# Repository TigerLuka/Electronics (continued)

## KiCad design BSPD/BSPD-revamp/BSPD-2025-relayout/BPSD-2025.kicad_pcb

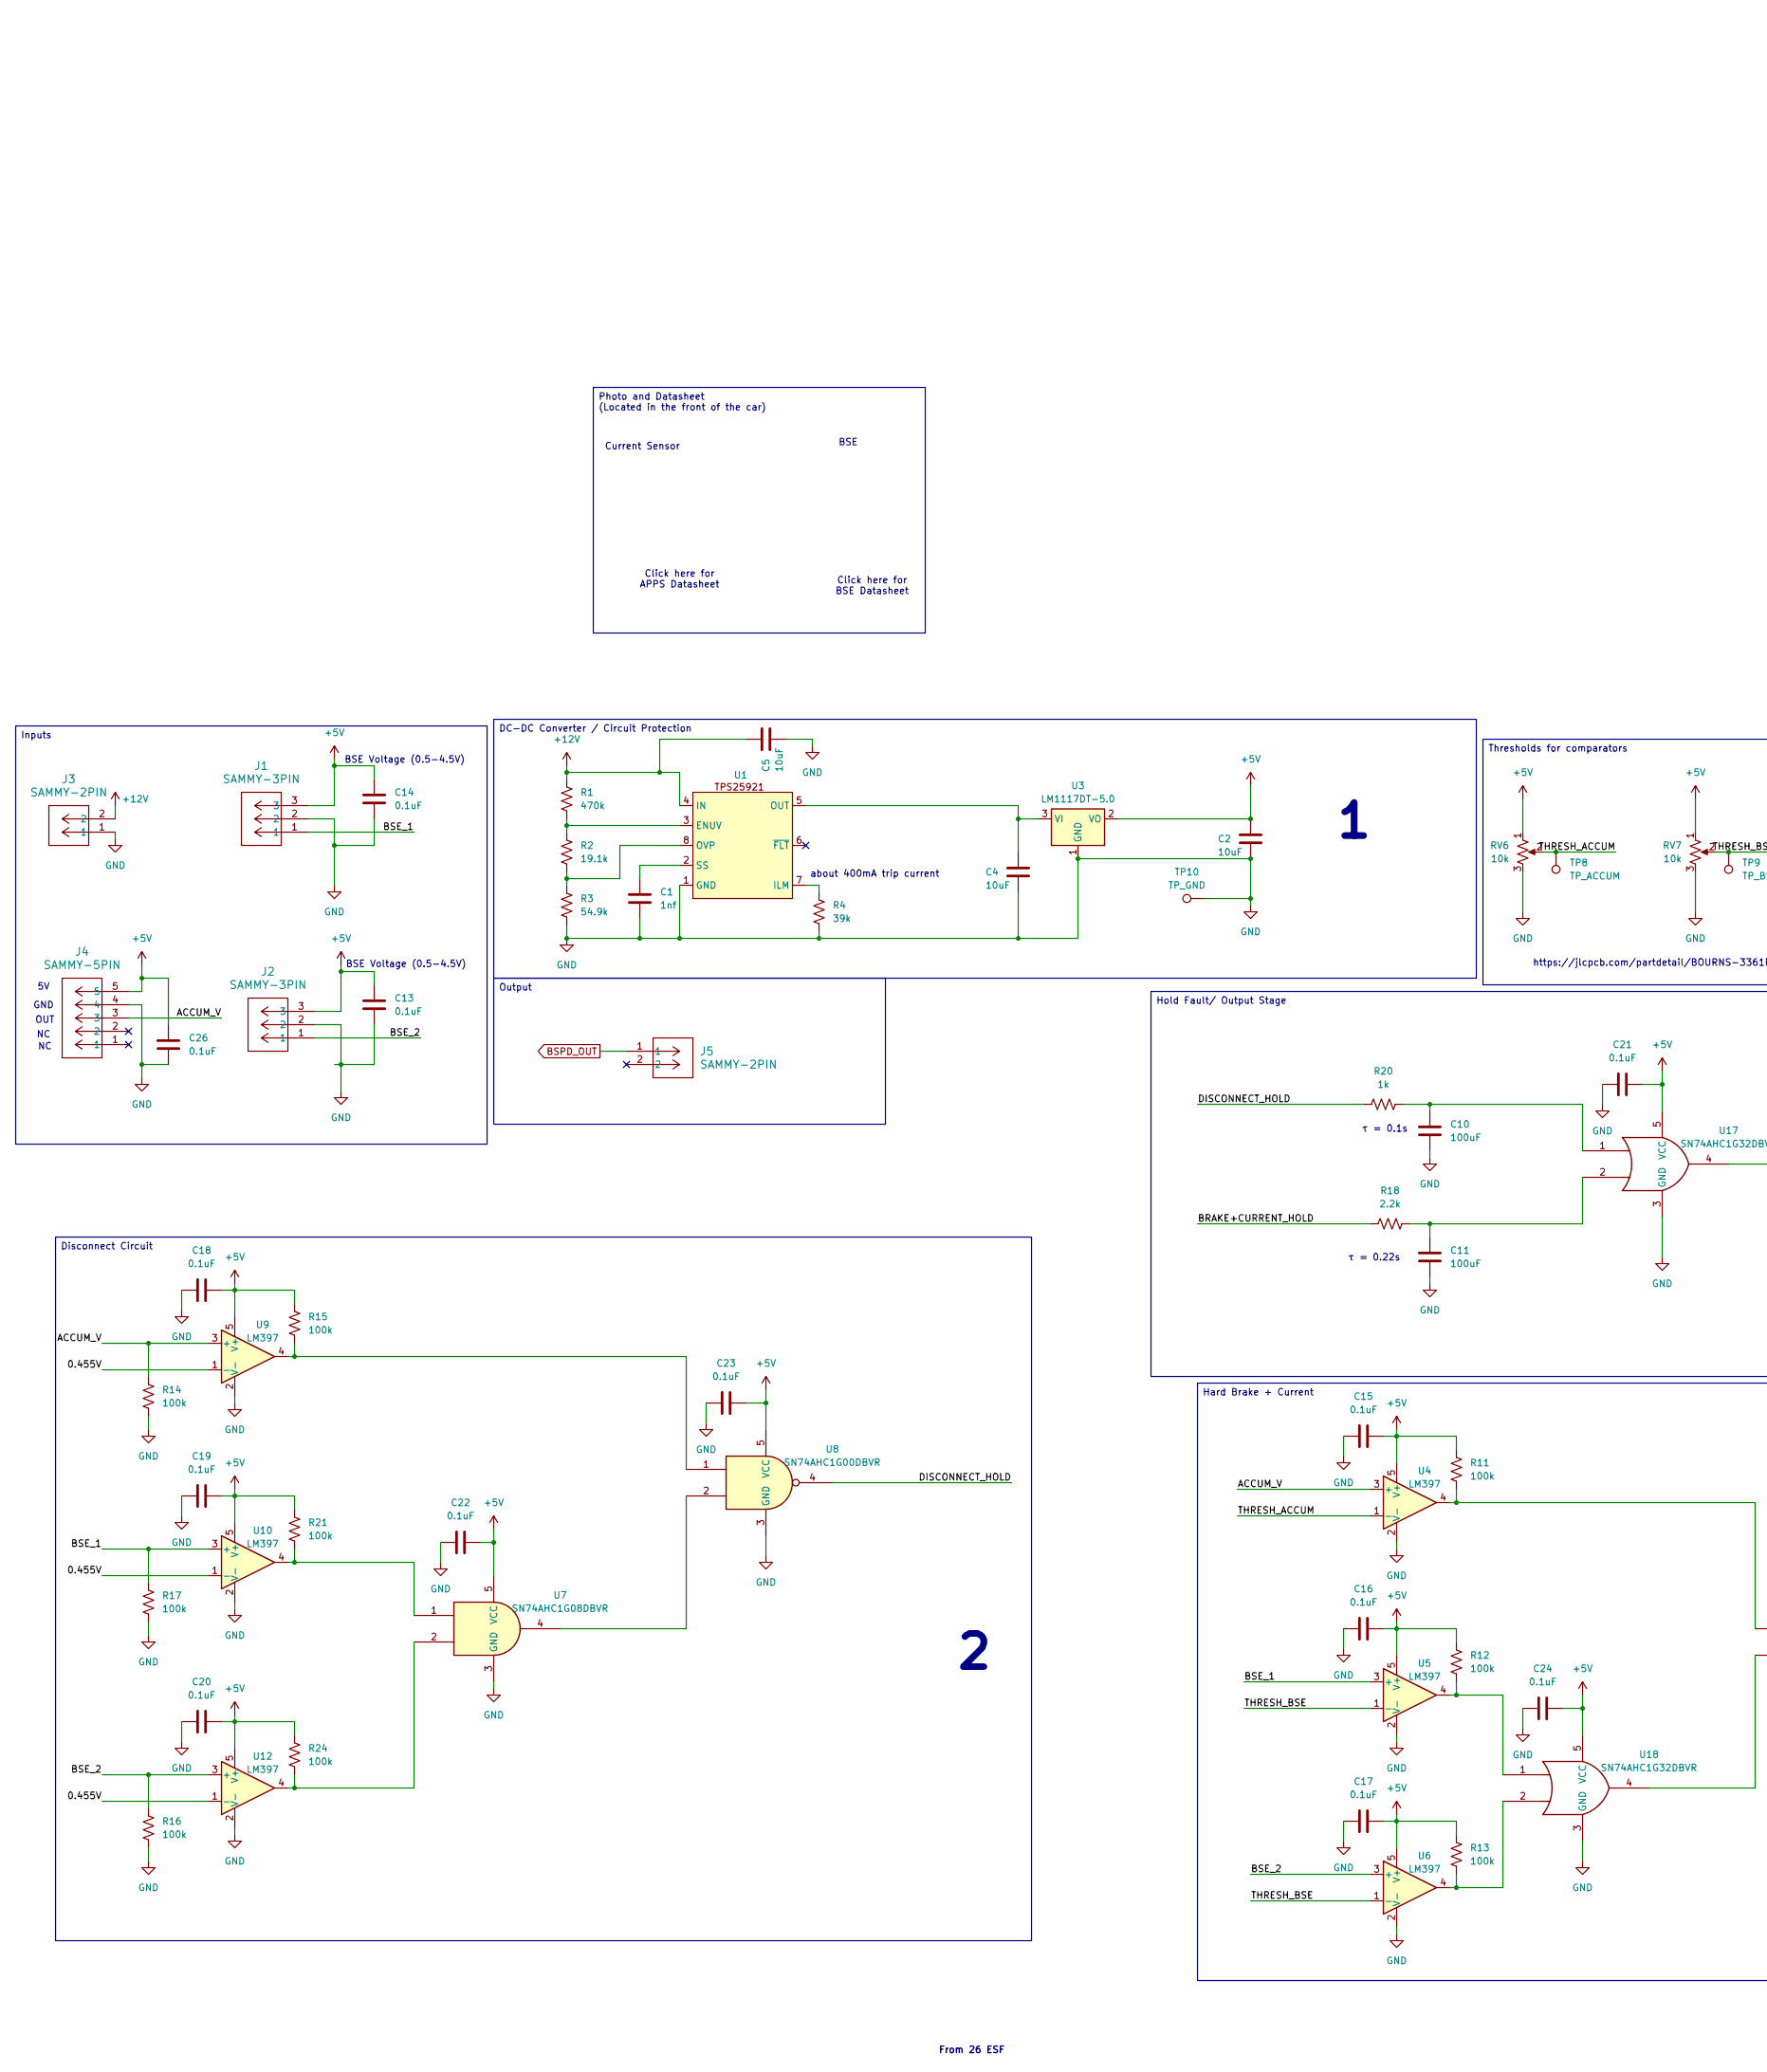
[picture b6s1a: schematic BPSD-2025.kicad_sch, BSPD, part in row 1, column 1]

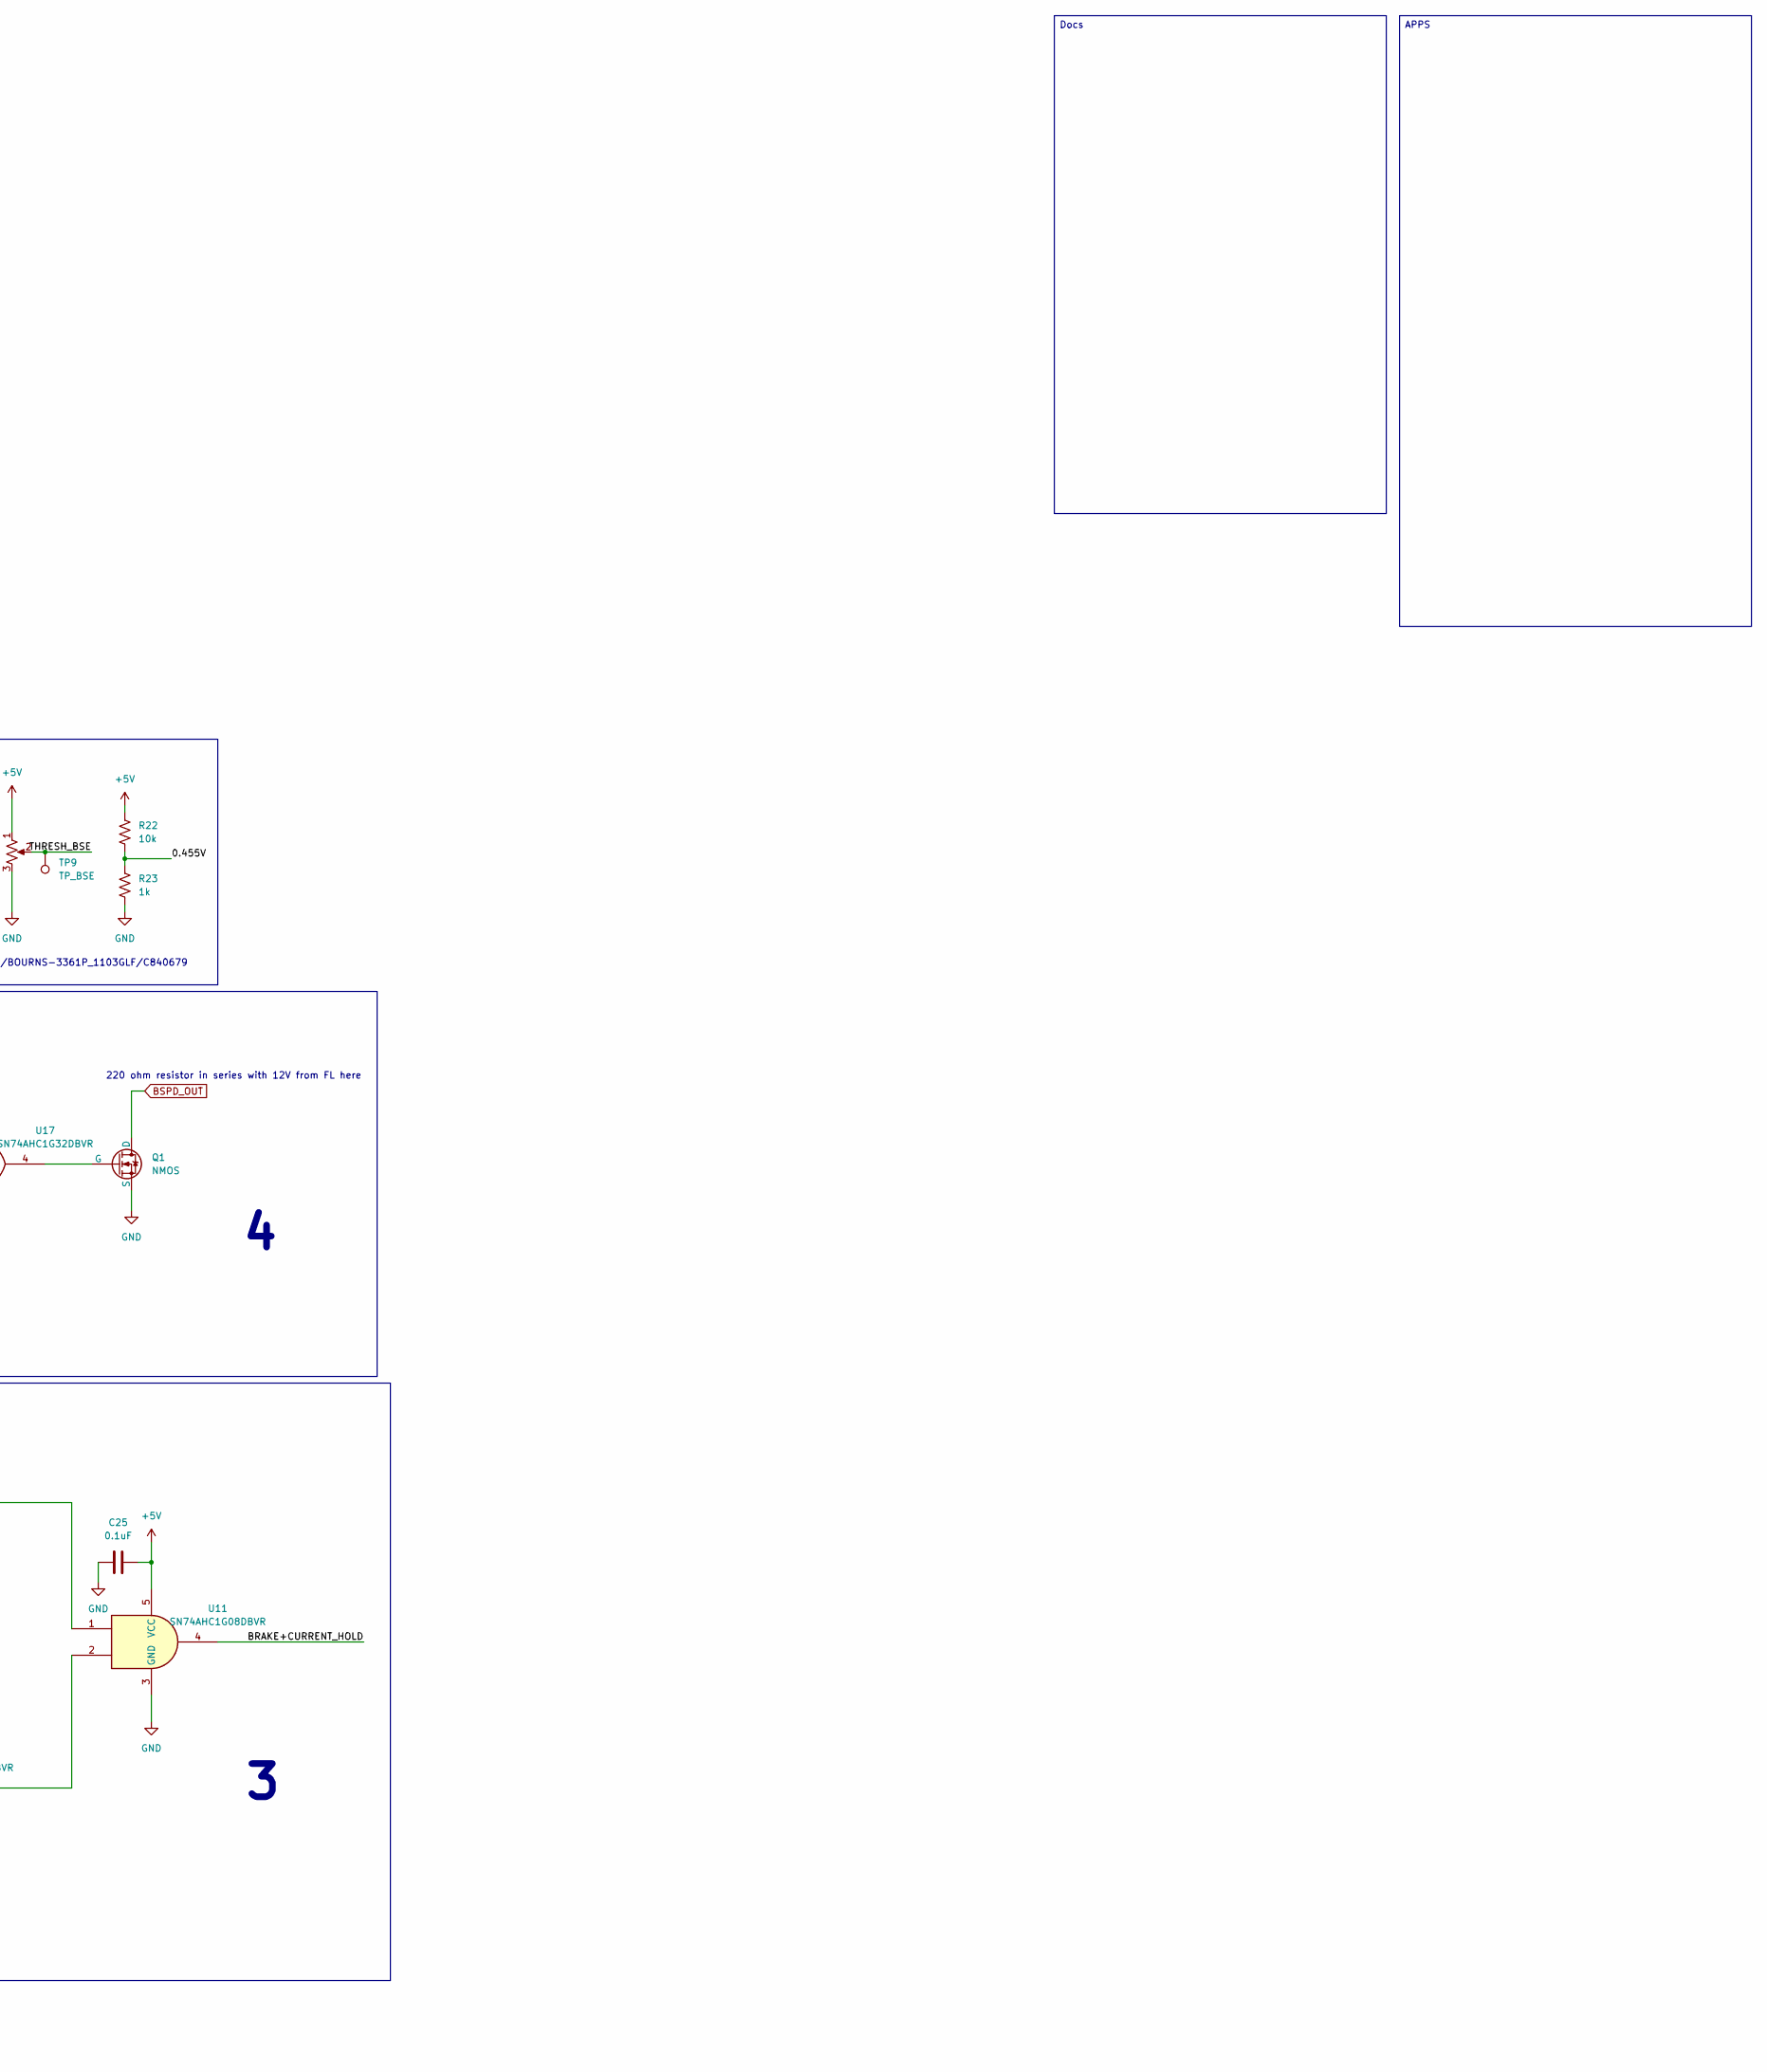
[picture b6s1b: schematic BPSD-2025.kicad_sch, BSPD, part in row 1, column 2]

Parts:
C1: 1nf; C_1206_3216Metric; JLC# C1845
C2, C4, C5: 10uF; C_1206_3216Metric; JLC# C1849
C10, C11: 100uF; C_1206_3216Metric; JLC# C782156
C13, C14, C15, C16, C17, C18, C19, C20, C21, C22, C23, C24, C25, C26: 0.1uF; C_1206_3216Metric; JLC# C1945
J1, J2: SAMMY-3PIN
J3, J5: SAMMY-2PIN
J4: SAMMY-5PIN
Q1: NMOS; SOT-23; JLC# C151421
R1: 470k; R_1210_3225Metric; JLC# C48392111
R2: 19.1k; R_1210_3225Metric; JLC# C784281
R3: 54.9k; R_1206_3216Metric; JLC# C323092
R4: 39k; R_1210_3225Metric; JLC# C728378
R11, R12, R13, R14, R15, R16, R17, R21, R24: 100k; R_1210_3225Metric; JLC# C230004
R18: 2.2k; R_1210_3225Metric; JLC# C230160
R20, R23: 1k; R_1210_3225Metric
R22: 10k; R_1210_3225Metric; JLC# C309586
RV6, RV7: 10k; Potentiometer_Bourns_3296W_Vertical; JLC# C118954
TP8: TP_ACCUM; TestPoint_Pad_D1.5mm
TP9: TP_BSE; TestPoint_Pad_D1.5mm
TP10: TP_GND; TestPoint_Pad_D1.5mm
U1: SOIC-8_3.9x4.9mm_P1.27mm; JLC# C189199
U3: LM1117DT-5.0; TO-252-3_TabPin2
U4, U5, U6, U9, U10, U12: LM397; SOT-23-5; JLC# C132076
U7, U11: SN74AHC1G08DBVR; SOT-23-5; JLC# C7467
U8: SN74AHC1G00DBVR; SOT-23-5; JLC# C350556
U17, U18: SN74AHC1G32DBVR; SOT-23-5; JLC# C7470

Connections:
+5V: C2.1, C13.1, C14.1, C15.2, C16.2, C17.2, C18.2, C19.2, C20.2, C21.2, C22.2, C23.2, C24.2, C25.2, C26.1, J1.3, J2.3, J4.5, R11.2, R12.2, R13.2, R15.2, R21.2, R22.2, R24.2, RV6.1, RV7.1, U3.2 (VO), U4.5 (V+), U5.5 (V+), U6.5 (V+), U7.5 (VCC), U8.5 (VCC), U9.5 (V+), U10.5 (V+), U11.5 (VCC), U12.5 (V+), U17.5 (VCC), U18.5 (VCC)
+12V: C5.1, J3.2, R1.1, U1.4 (IN)
/0.455V: R22.1, R23.2, U9.1 (-), U10.1 (-), U12.1 (-)
/ACCUM_V: J4.3, R14.2, U4.3 (+), U9.3 (+)
/BRAKE+CURRENT_HOLD: R18.1, U11.4
/BSE_1: J1.1, R17.2, U5.3 (+), U10.3 (+)
/BSE_2: J2.1, R16.2, U6.3 (+), U12.3 (+)
/DISCONNECT_HOLD: R20.1, U8.4
/THRESH_ACCUM: RV6.2, TP8.1, U4.1 (-)
/THRESH_BSE: RV7.2, TP9.1, U5.1 (-), U6.1 (-)
BSPD_OUT: J5.1, Q1.1 (D)
GND: C1.2, C2.2, C4.2, C5.2, C10.2, C11.2, C13.2, C14.2, C15.1, C16.1, C17.1, C18.1, C19.1, C20.1, C21.1, C22.1, C23.1, C24.1, C25.1, C26.2, J1.2, J2.2, J3.1, J4.4, Q1.3 (S), R3.2, R4.2, R14.1, R16.1, R17.1, R23.1, RV6.3, RV7.3, TP10.1, U1.1 (GND), U3.1 (GND), U4.2 (V-), U5.2 (V-), U6.2 (V-), U7.3 (GND), U8.3 (GND), U9.2 (V-), U10.2 (V-), U11.3 (GND), U12.2 (V-), U17.3 (GND), U18.3 (GND)
unnamed: C10.1, R20.2, U17.1
unnamed: C11.1, R18.2, U17.2
unnamed: Q1.2 (G), U17.4
unnamed: R11.1, U4.4, U11.1
unnamed: R12.1, U5.4, U18.1
unnamed: R13.1, U6.4, U18.2
unnamed: R15.1, U8.1, U9.4
unnamed: R21.1, U7.1, U10.4
unnamed: R24.1, U7.2, U12.4
unnamed: R1.2, R2.1, U1.3 (ENUV)
unnamed: R4.1, U1.7 (ILM)
unnamed: C4.1, U1.5 (OUT), U3.3 (VI)
unnamed: R2.2, R3.1, U1.8 (OVP)
unnamed: C1.1, U1.2 (SS)
unnamed: U7.4, U8.2
unnamed: U11.2, U18.4

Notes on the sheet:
BSE Voltage (0.5-4.5V)
BSE
GND
220 ohm resistor in series with 12V from FL here
about 400mA trip current
τ = 0.1s
Click here for APPS Datasheet
OUT
https://jlcpcb.com/partdetail/BOURNS-3361P_1103GLF/C840679
τ = 0.22s
From 26 ESF
Current Sensor
Click here for BSE Datasheet
Inputs
Hard Brake + Current
Docs
APPS
Photo and Datasheet (Located in the front of the car)
DC-DC Converter / Circuit Protection
Disconnect Circuit
Hold Fault/ Output Stage
Thresholds for comparators
Output

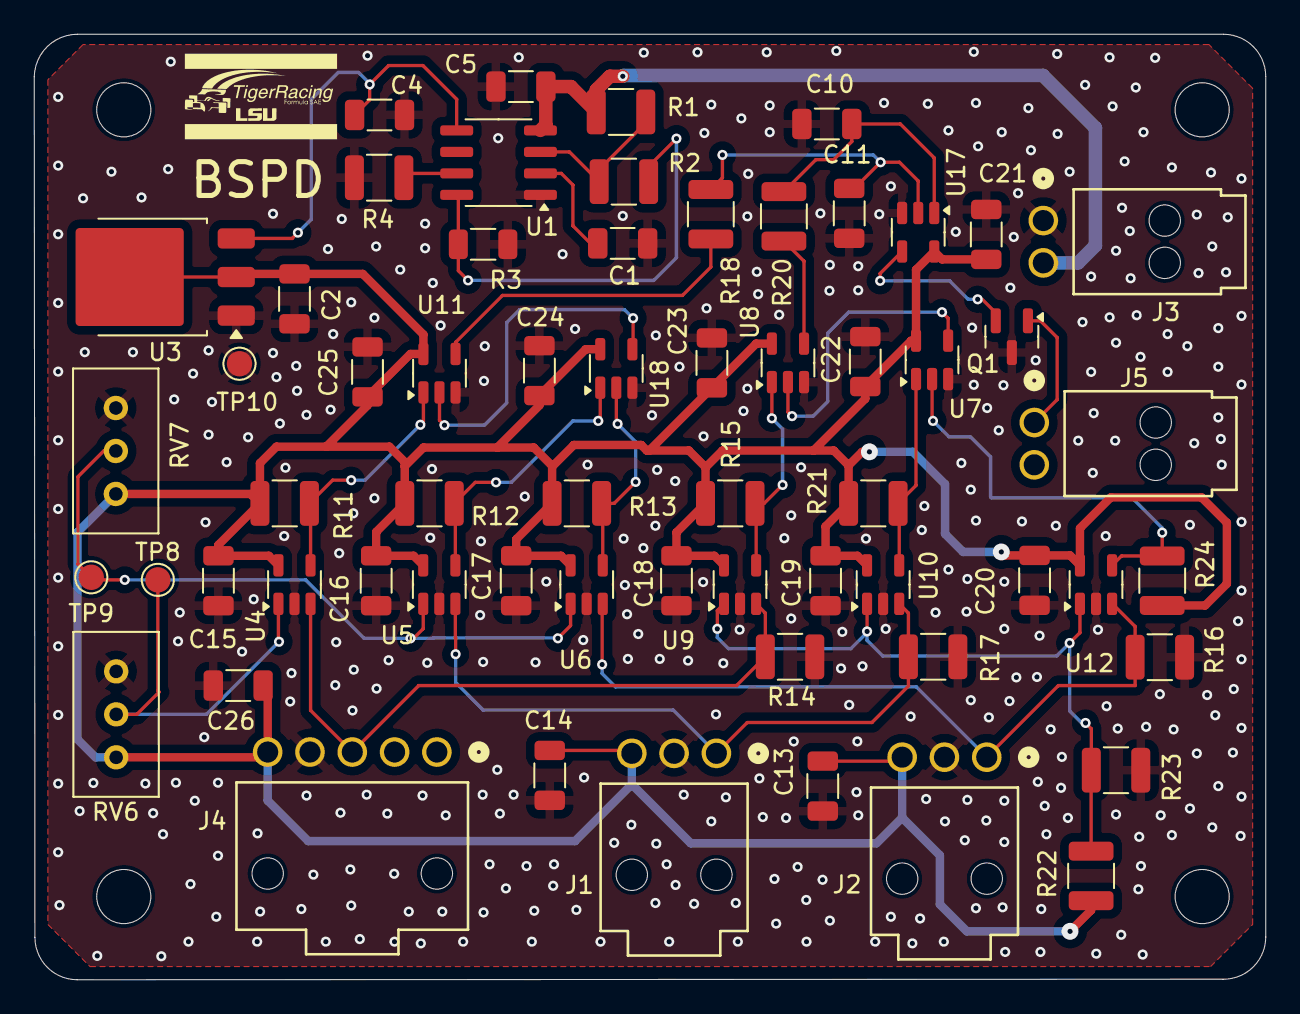
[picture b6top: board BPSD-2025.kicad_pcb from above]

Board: 2 copper layers, 72.8 x 55.9 mm, 61 parts (0 on the bottom side), 28 nets.

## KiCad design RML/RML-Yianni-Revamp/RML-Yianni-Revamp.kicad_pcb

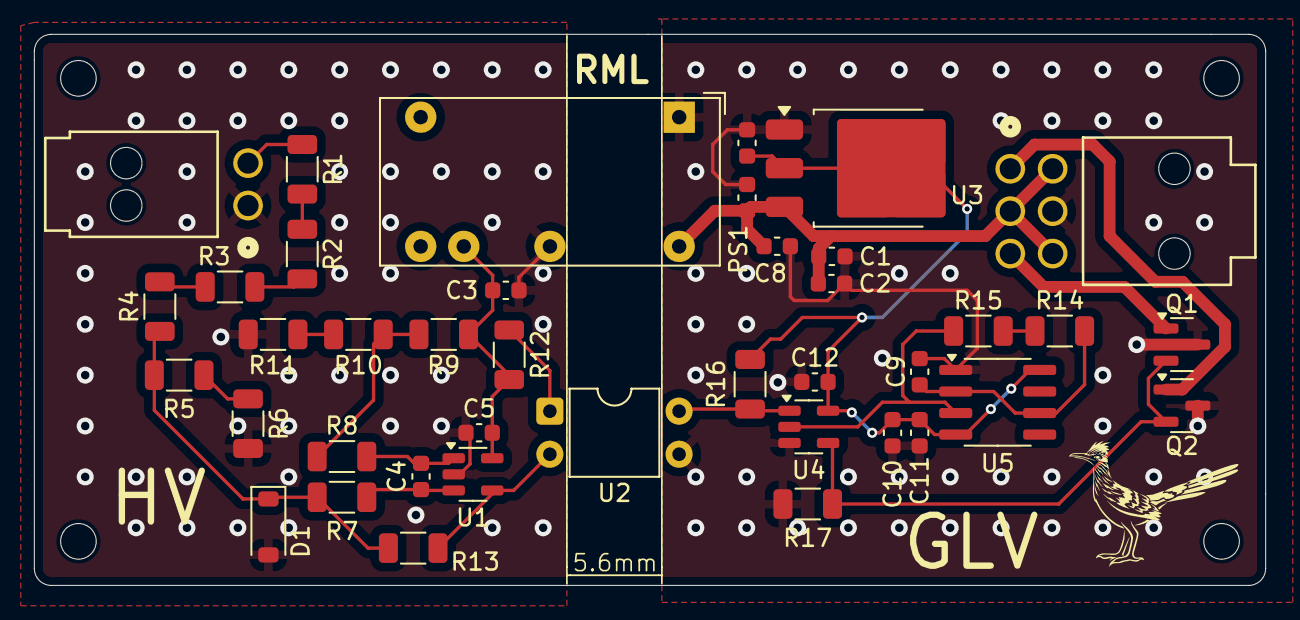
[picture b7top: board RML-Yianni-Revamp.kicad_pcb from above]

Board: 2 copper layers, 72.6 x 32.5 mm, 40 parts (0 on the bottom side), 24 nets.

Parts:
C1, C3, C4, C6, C7: 10u; C_0603_1608Metric
C2, C8, C9, C10: 1u; C_0603_1608Metric
C5, C11, C12: 100n; C_0603_1608Metric
D1: 12V; D_SOD-123
J1: Tractive; SAMMY-2PIN
J3: SAMMY-6PIN
PS1: IA1212D; Converter_DCDC_XP_POWER-IAxxxxD_THT
Q1, Q2: NMOS; SOT-23
R1, R2, R3, R4: 249k; R_1206_3216Metric
R5: 49k9; R_1206_3216Metric
R6: 2k2; R_1206_3216Metric
R7, R8: 100; R_1206_3216Metric
R9: 75k; R_1206_3216Metric
R10: 24k; R_1206_3216Metric
R11: 900; R_1206_3216Metric
R12: 1k; R_1206_3216Metric
R13: 1M; R_1206_3216Metric
R14: 47k; R_1206_3216Metric
R15, R17: 100k; R_1206_3216Metric
R16: 10k; R_1206_3216Metric
U1: LM397; SOT-23-5
U2: SFH617A-1; DIP-4_W7.62mm
U3: LM1117DT-5.0; TO-252-3_TabPin2
U4: 74AHC1G02; SOT-23-5
U5: LM555xM; SOIC-8_3.9x4.9mm_P1.27mm

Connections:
+5V: C7.1, C10.1, C11.1, C12.2, R16.1, U3.2 (VO), U4.5 (VCC), U5.4 (R), U5.8 (VCC)
+12V: C1.1, C2.1, C6.1, C8.1, J3.2, J3.4, J3.6, PS1.3 (+Vin), U3.3 (VI)
/ISO_+12V: C3.1, C5.2, PS1.5 (+Vout), R9.1, R12.2, U1.5 (V+)
/RML1-: J3.3, Q1.1 (D)
/RML2-: J3.1, Q2.1 (D)
/THRESH: C9.1, R14.1, U5.2 (TR), U5.6 (THR)
/TS+: J1.2, R1.1
/Vref: R8.1, R9.2, R10.1
CLOCK: R15.2, U4.2, U5.3 (Q)
GND: C1.2, C2.2, C6.2, C7.2, C8.2, C9.2, C10.2, C11.2, C12.1, J3.5, PS1.1 (-Vin), Q1.3 (S), Q2.3 (S), R17.1, U2.3, U3.1 (GND), U4.3 (GND), U5.1 (GND)
GNDPWR: C3.2, C5.1, D1.2 (A), J1.1, PS1.4 (-Vout), R6.2, R11.2, U1.2 (V-)
unnamed: D1.1 (K), R4.2, R5.1, R7.1, R13.1
unnamed: Q1.2 (G), Q2.2 (G), R17.2, U4.4
unnamed: R1.2, R2.1
unnamed: R2.2, R3.1
unnamed: R3.2, R4.1
unnamed: R5.2, R6.1
unnamed: R10.2, R11.1
unnamed: R12.1, U2.1
unnamed: R13.2, U1.4, U2.2
unnamed: R14.2, R15.1
unnamed: R16.2, U2.4, U4.1
unnamed: C4.1, R7.2, U1.3 (+)
unnamed: C4.2, R8.2, U1.1 (-)

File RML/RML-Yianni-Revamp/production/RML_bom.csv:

Designator,Footprint,Quantity,Value,LCSC Part #
"C1, C3, C4, C6, C7",0603,5,10u,
"C10, C2, C8, C9",0603,4,1u,
"C11, C12, C5",0603,3,100n,
D1,D_SOD-123,1,12V,
J1,SAMMY-2PIN,1,Tractive,
J3,SAMMY-6PIN,1,SAMMY-6PIN,
PS1,Converter_DCDC_XP_POWER-IAxxxxD_THT,1,IA1212D,
"Q1, Q2",SOT-23,2,NMOS,
"R1, R2, R3, R4",1206,4,249k,C34578
R10,1206,1,24k,
R11,1206,1,900,
R12,1206,1,1k,
R13,1206,1,1M,
R14,1206,1,47k,
"R15, R17",1206,2,100k,
R16,1206,1,10k,
R5,1206,1,49k9,
R6,1206,1,2k2,
"R7, R8",1206,2,100,
R9,1206,1,75k,
U1,SOT-23-5,1,LM397,
U2,DIP-4_W7.62mm,1,SFH617A-1,
U3,TO-252-3_TabPin2,1,LM1117DT-5.0,
U4,SOT-23-5,1,74AHC1G02,
U5,SOIC-8_3.9x4.9mm_P1.27mm,1,LM555xM,

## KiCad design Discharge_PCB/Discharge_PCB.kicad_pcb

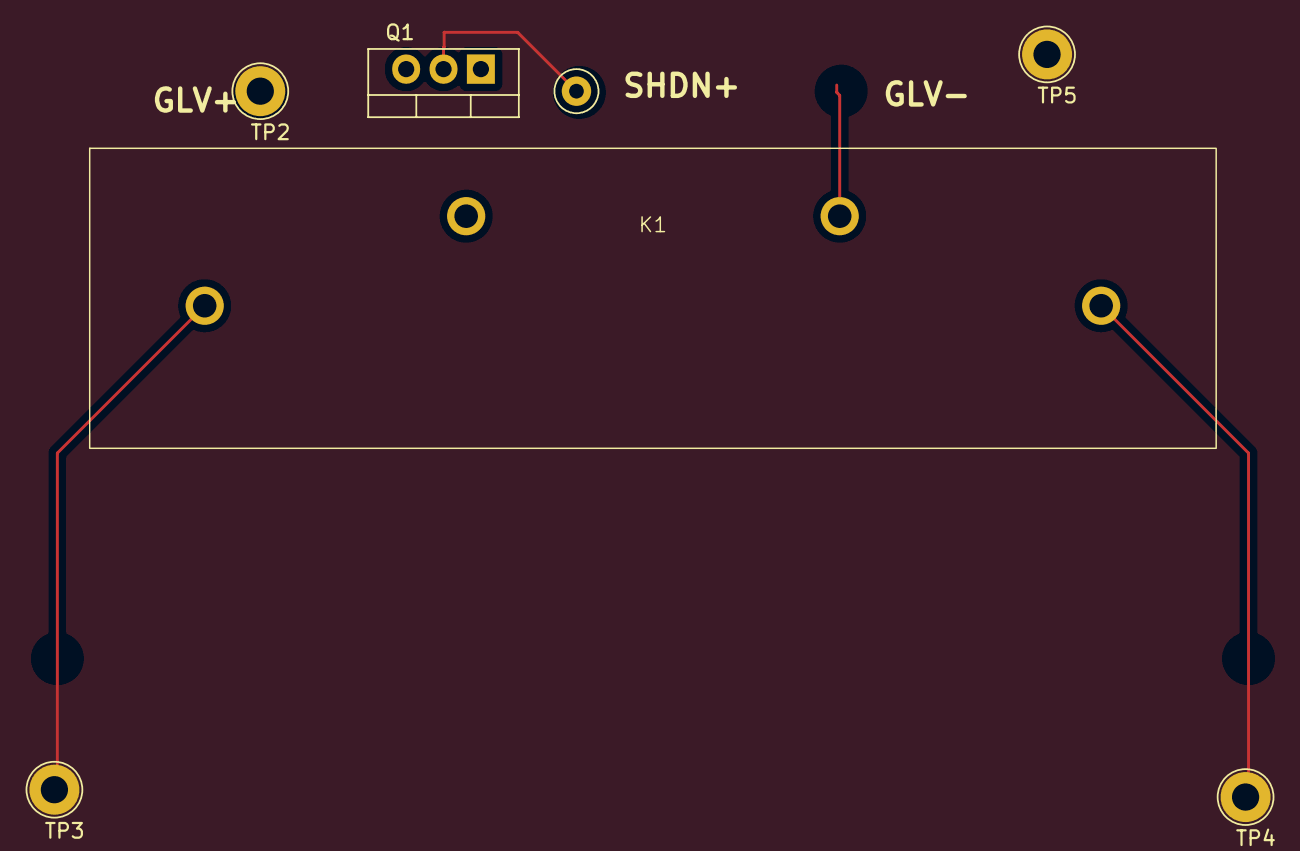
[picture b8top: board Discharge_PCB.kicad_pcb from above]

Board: 2 copper layers, 7 parts (0 on the bottom side), 2 nets.

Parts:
K1: Relay_SPST-NC; Relay_SPST_NC_COMUS
Q1: PMOS; TO-220-3_Vertical
TP1: SHDN; TestPoint_Loop_D1.80mm_Drill1.0mm_Beaded
TP2: +12V; TestPoint_Loop_D2.50mm_Drill1.85mm
TP3: HV_In; TestPoint_Loop_D2.50mm_Drill1.85mm
TP4: HV_Out; TestPoint_Loop_D2.50mm_Drill1.85mm
TP5: -12V; TestPoint_Loop_D2.50mm_Drill1.85mm

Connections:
unnamed: Q1.2 (G), TP1.1
unnamed: Q1.3 (S), TP2.1

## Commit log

2025-08-04 SamplePush3000
    meeting demo
2025-08-04 Charging
    Falstad logic update
2025-08-20 charging THT parts updated for testing
2025-08-24 Lots of fixes on FL
2025-08-26 changed labeling on charging test schematic
2025-08-26 changed led resistor values from 270 to 2k
2025-08-26 IMD switched from Active High to Active low
2025-08-26 fixed logic for bms/imd signals, might still float tell vinh confusing
2025-08-27 Added input datasheets to BSPD
2025-08-27 fixed falstad charging
2025-08-28 Added revised BSPD-2025
2025-08-29 Worked on BSPD
2025-08-29 APPS DCDC converter switch-up
2025-08-29 BSPD Added comparator
2025-08-29 fixed logic i think
2025-08-29 Fault Latch - THT
2025-08-29 Put BPSD foorprints
2025-08-29 Added fuse to input of pcb and data sheets
    easy for noobs (Jacob)
2025-08-29 fixed connector wiring
    fuse is off board
2025-08-30 Hopefully BSPD is Final
2025-08-30 Added Precharge
2025-08-30 Checked RML
2025-08-30 BSPD Stuff
2025-08-30 Added docs to Fault Latch
2025-08-30 Added more docs to Fault Latch
2025-08-30 Charging PCB Docs
2025-08-30 JACOB meeting
2025-09-02 Through Hole Fault Latch 2
2025-09-02 RML through hole part 1
2025-09-02 RML Through hole BOM updated
2025-09-02 Precharge missing schematic footprints
2025-09-03 offset board
2025-09-03 ewrw
2025-09-05 New Member tutorial
2025-09-05 Added Flashlight
2025-09-05 added flashlight file
2025-09-05 Vinh forced me to
2025-09-05 Creating a flashlight cuz im amazing
2025-09-05 merging to main
2025-09-05 Revert "added flashlight"
    This reverts commit 114a32e43cf8345afc968644d8f8c5cfb0c2f7a2.
2025-09-05 Revert "added flashlight"
    This reverts commit b4e2d6eec8096a60974343692bd5bde10ad1bbf5.
2025-09-10 Removed New member folder
2025-10-01 added fan and saftey circuit pcb
2025-10-01 test
2025-10-02 Fixed Fault Latch optocoupler
2025-10-05 Description of work done in commit
2025-10-14 Safety Circuit PCB First Prototype
    First prototype board and schematic for safety circuit. Falstad simulation for safety circuit demonstrating how it works is https://tinyurl.com/275r7dj9
2025-10-14 Flip connectors, make more sane pin assignments for connections, get nicer tracks, and make dimensions reasonable
2025-10-14 Add mounting holes, round corners, add silkscreen logo and Charlie Brown
2025-10-15 Yianni BSPD eFuse
2025-10-15 Added Discharge
    need to finish custom symbol, and layout
2025-10-16 Implement improvement advice from Jacob
    Add ground vias next to all NMOS grounds
    Change pull-down resistors at gates of NMOS to 100k from 1k, and change datasheet and resistor fields (part #, JLC Part #, etc...) accordingly
    Make 12V power track 0.5 mm from 0.3mm
    Add falstad simulation text file to Safety Circuit project
    ERC and DRC still all pass
2025-10-16 added data sheet for resistor
    yianni make footprint for 3k
2025-10-21 combined precharge/discharge
2025-10-21 Revised Fault Latch Layout
    Fixed the schematic, did layout and wiring. Check for size and missed wires.
2025-10-21 added labels and pull down resistor
2025-10-23 BSPD schematic change & RML revamp
2025-10-26 JLC Board Template for Board Setup Constraints
2025-10-26 Add Sammy connector footprint to Safety Circuit PCB
    The PCB layout still needs to be redone once again to actually fit the connector. It seems like it will have to be extended around 0.8 inches. at a minimum.
2025-10-26 Create BSPD/BSPD-revamp/BSPD-revamp-layout
    Trying to get BSPD a little smaller for fitting into the GLV box. Somewhat worked. Still a few problems with how the front and back ground zones connect, and the differences between the GNDPWR pin an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
2025-10-27 charging pcb layout
    charging pcb ready to order, would like funny logo on there
2025-10-27 charging pcb
    terminated unused SR latch/Nand gate inputs
2025-10-28 Fault Latch Layout revised
2025-10-28 Safety Circuit - Add Sammy Connector, Generate BOM, Generate Gerber and Drill Files
    Safety circuit is about half an inch wider and half and inch less tall now
2025-10-30 breath of fresh air
2025-10-30 Connector refactor
    Add nanofit for input and output, remove two 8-pin connectors. Still need to stitch board and regenerate gerbers.
2025-10-30 Precharge
    deleted empty ground plane
2025-10-31 Safety Circuit Logical Refactor
    After realizing that safety circuit would definitely not work, I remade it so that it would.
2025-10-31 Precharge
    Fixed Ground plane distance, added new DC converter, fixed precharge resistor value
2025-10-31 added discharge relay and resistor footprints to precharge board
    still need all part numbers but ffootprints are selected, go shopping on JLC
2025-11-04 Fault Latch Updates
2025-11-04 precharge
    fixed board edges
2025-11-04 Add some more descriptive drawings to back silkscreen
2025-11-04 Move output connector to right side and re-connect board
    Gerbers and Drills are regenerated, and 3D model is regenerated as well.
2025-11-05 Fault Latch Layout Pre-Bom 2025 check
2025-11-05 Fault Latch pre-BOM check
2025-11-05 RML BOM
2025-11-05 Safety Circuit changed 100k to the correct part
2025-11-05 Reroute BSPD and adjust connector spacing
    The other routing was atrocious. Also regenerated gerbers, drills, and 3d model.
2025-11-05 Fault Latch BOM Checked and Safety Circuit
2025-11-05 precharge/discharge. charging
    removed discharge ffrom precharge and put it on board out of battery, updqted charging according to discharge
2025-11-06 Remove pull down resistors at MOSFET gates and increase sizes of traces
    Also some more nice via tracing.
2025-11-06 Added Measuring points to Fault Latch
2025-11-06 Fault Latch and RML BOM created
2025-11-08 Molex Microfit
2025-11-08 Precharge Testing
    Uploaded precharge testing data, settled on 1.5k ohm resistor to precharge MC around 1s
2025-11-10 Connectors, time delay, vreferences
2025-11-10 BSPD, Precharge, and Charging PCB BOMs pulled
2025-11-11 BOM stuff
2025-11-12 12-Pin connector changed to Molex Nano
2025-11-12 Add Updated Safety Circuit BOM
2025-11-15 precharge dcdc
    updated precharge dcdc converter to match footprint
2025-12-19 started TS schematic
    TS schematic for ESF
2026-01-04 Updated TS Schematics 4 esf
    esf dtuff
2026-01-08 Charging FIxes
    NMOS's Q1-4 had the wrong symbol as DGS, updated symbol and board with NMOS's Q1-4 to now have the correct symbol of GDS, to match the datasheet.
2026-01-08 Discharge fixes
    Fixed footprint and symbol for discharge NMOS
2026-01-08 prechaarge
    fixed precharge footprin
2026-01-08 precharge fixes
    fix
2026-01-13 Fault Latch Spring Semester
    Fixed TSSI, Logic, and everything.
2026-01-14 Changed Optocoupler to mosfet and added resistor to tssi red
2026-01-15 Charging fixes
    added pull down resistor to imd signal so it faults when unconnected
2026-01-15 Add .gitignore for KiCad project files
2026-01-15 Fault Latch V3
2026-01-15 Folder Cleanup
2026-01-21 Fixed Discharge NMOS
    Drain was connected to ground
2026-02-07 Fault Latch reivision
    Currently fixing the 2026 iteration of the fault latch.
2026-02-09 Discharge
    guys its gonns work this time
2026-02-10 charging
    fixed issue where Q3 and Q4 mosfets had source and drain swapped
